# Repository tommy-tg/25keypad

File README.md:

# 25keypad
25 keys Macropad based on RP2040 MCU, programmable, running KMK firmware

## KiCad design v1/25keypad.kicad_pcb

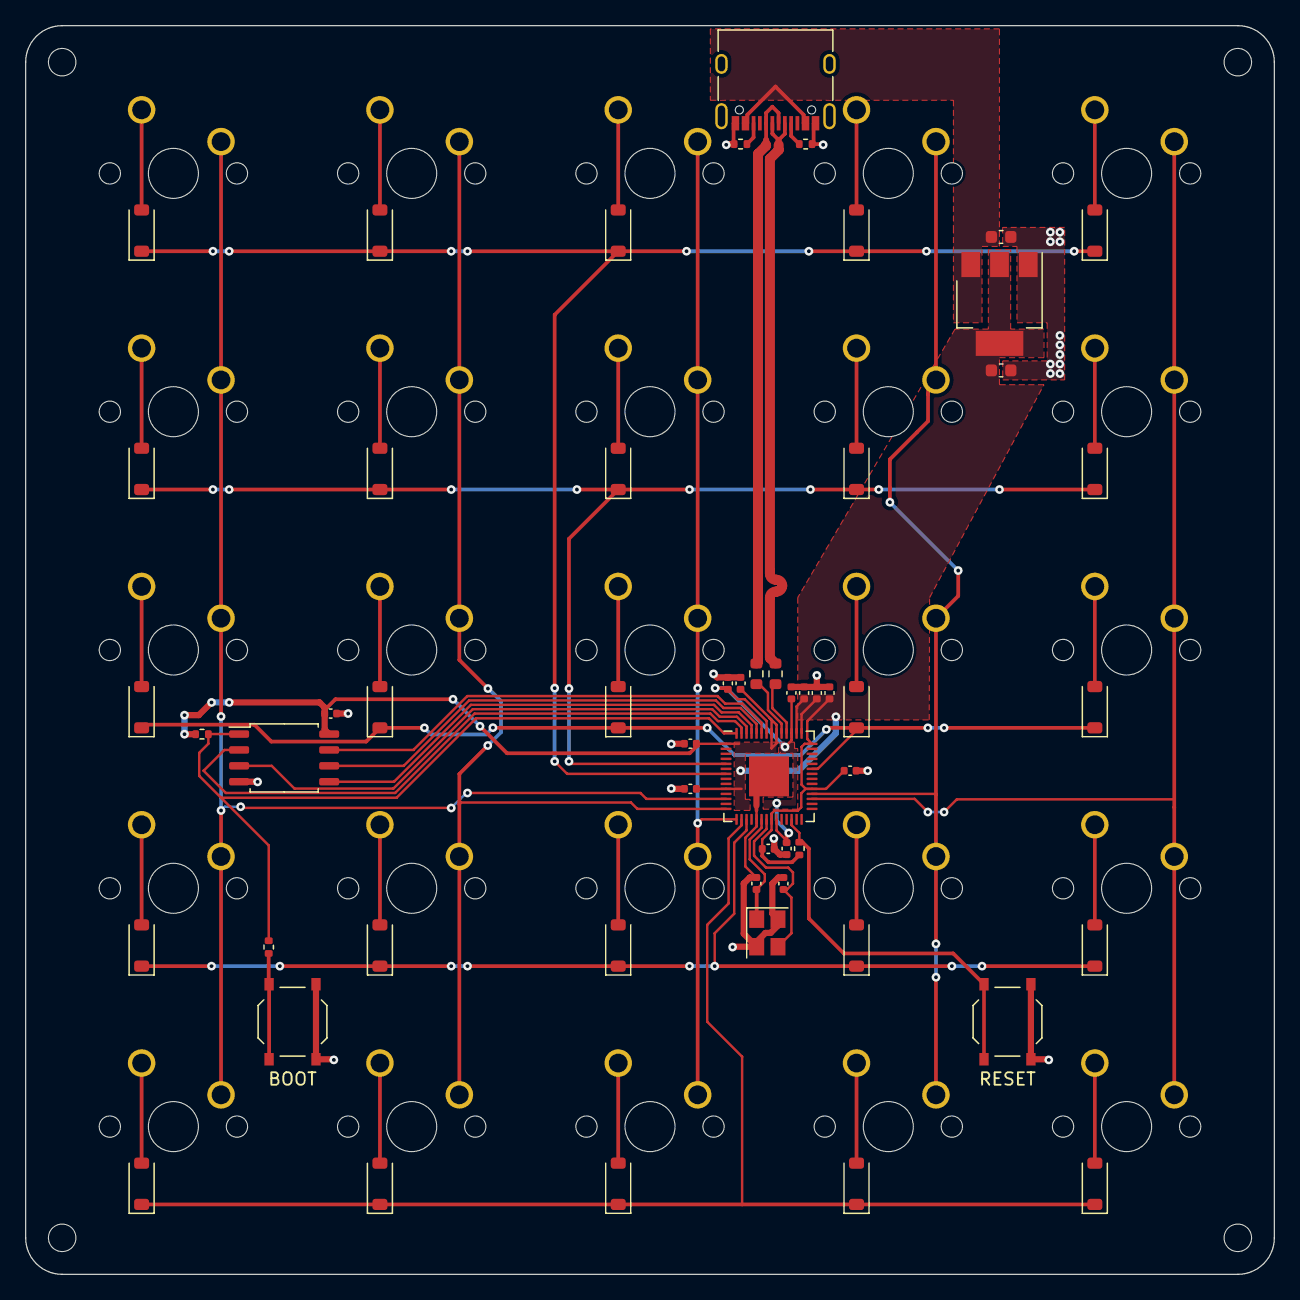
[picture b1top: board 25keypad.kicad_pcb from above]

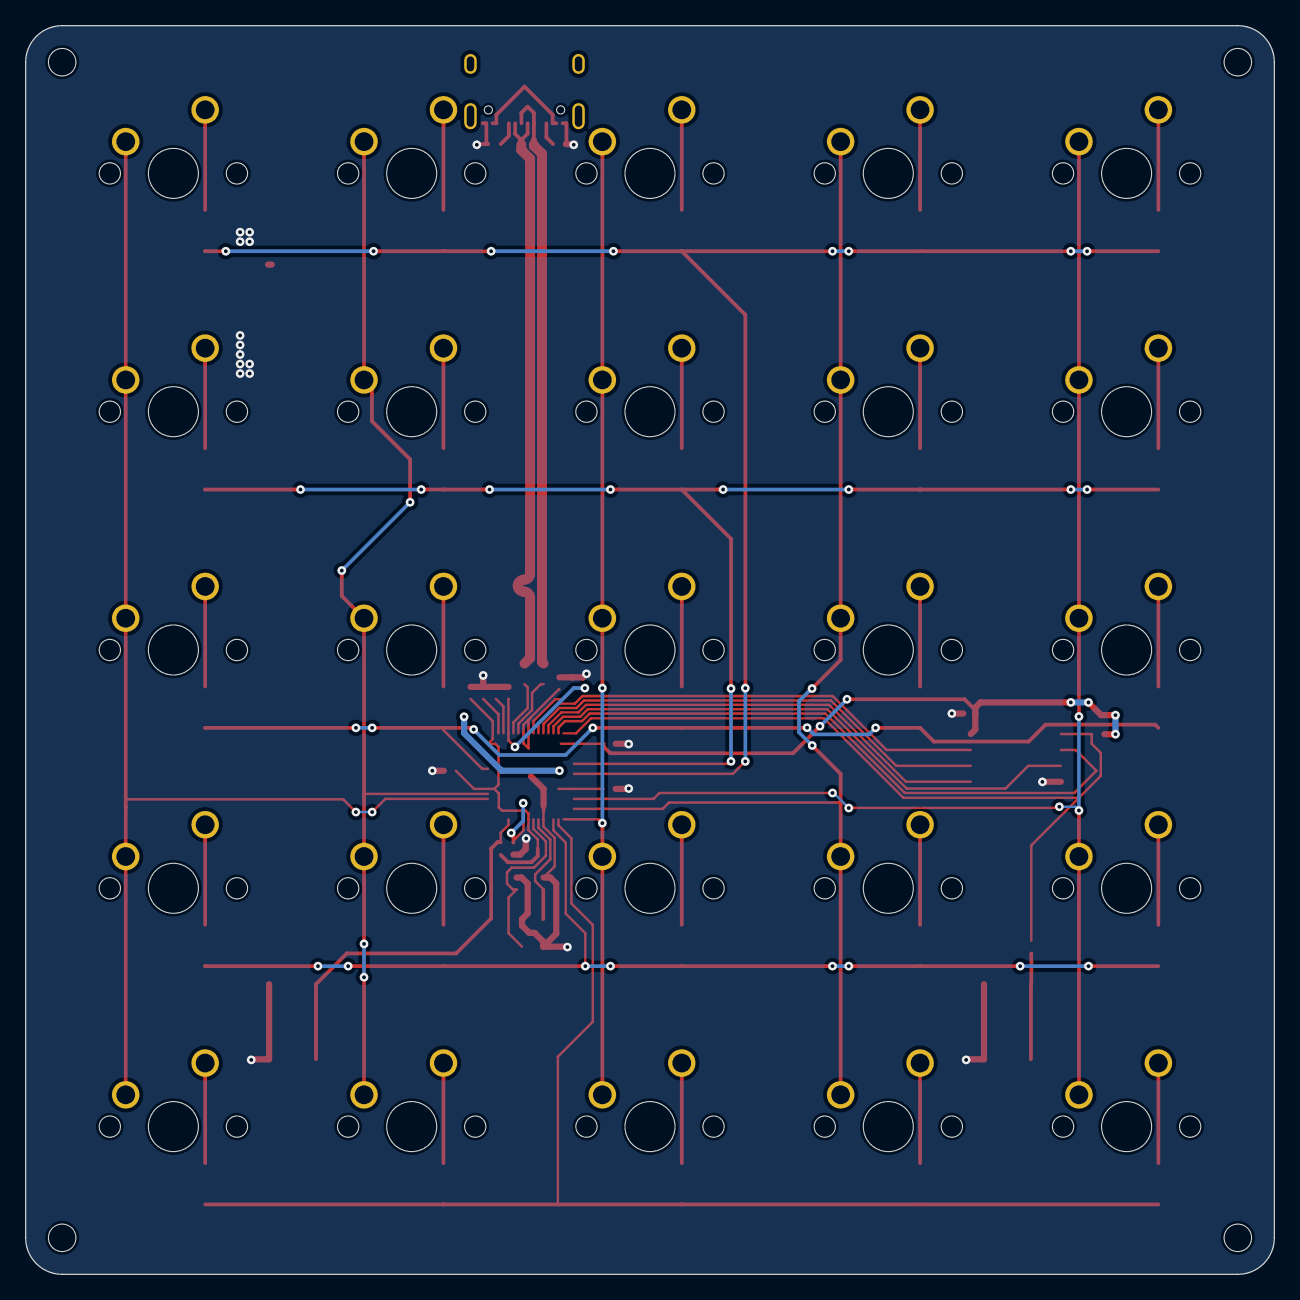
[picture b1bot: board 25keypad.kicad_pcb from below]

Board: 2 copper layers, 99.8 x 99.8 mm, 84 parts (25 on the bottom side), 55 nets.

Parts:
C1, C2, C3, C4, C5, C6, C7, C8, C9, C16: 100n; C_0402_1005Metric
C10, C11: 1u; C_0402_1005Metric
C12, C13: 10u; C_0603_1608Metric
C14, C15: 30p; C_0402_1005Metric
D1, D2, D3, D4, D5, D6, D7, D8, D9, D10, D11, D12, D13, D14, D15, D16, D17, D18, D19, D20, D21, D22, D23, D24, D25: D; D_SOD-123
H1, H2, H3, H4: MountingHole; MountingHole_2.2mm_M2
J1: USB_C_Receptacle_USB2.0; USB_C_Receptacle_XKB_U262-16XN-4BVC11
R1, R2: 27; R_0603_1608Metric
R3: 10k; R_0402_1005Metric
R4, R5: 5k1; R_0402_1005Metric
R6: DNP_10k; R_0402_1005Metric
R7: 1k; R_0402_1005Metric
SW1: KEY_1_00; SW_Cherry_MX_1.00u_PCB_UPDATED_FOOTPRINT_RIGHT_PIN_ASSIGNME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
SW2: KEY_2_01; SW_Cherry_MX_1.00u_PCB_UPDATED_FOOTPRINT_RIGHT_PIN_ASSIGNME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
SW3: KEY_3_02; SW_Cherry_MX_1.00u_PCB_UPDATED_FOOTPRINT_RIGHT_PIN_ASSIGNME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
SW4, SW5, SW10, SW15, SW20, SW25: KEY_4_03; SW_Cherry_MX_1.00u_PCB_UPDATED_FOOTPRINT_RIGHT_PIN_ASSIGNME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
SW6: KEY_5_10; SW_Cherry_MX_1.00u_PCB_UPDATED_FOOTPRINT_RIGHT_PIN_ASSIGNME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
SW7: KEY_6_11; SW_Cherry_MX_1.00u_PCB_UPDATED_FOOTPRINT_RIGHT_PIN_ASSIGNME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
SW8: KEY_7_12; SW_Cherry_MX_1.00u_PCB_UPDATED_FOOTPRINT_RIGHT_PIN_ASSIGNME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
SW9: KEY_8_13; SW_Cherry_MX_1.00u_PCB_UPDATED_FOOTPRINT_RIGHT_PIN_ASSIGNME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
SW11, SW16, SW21: KEY_9_20; SW_Cherry_MX_1.00u_PCB_UPDATED_FOOTPRINT_RIGHT_PIN_ASSIGNME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
SW12, SW17, SW22: KEY_10_21; SW_Cherry_MX_1.00u_PCB_UPDATED_FOOTPRINT_RIGHT_PIN_ASSIGNME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
SW13, SW18, SW23: KEY_11_22; SW_Cherry_MX_1.00u_PCB_UPDATED_FOOTPRINT_RIGHT_PIN_ASSIGNME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
SW14, SW19, SW24: KEY_12_23; SW_Cherry_MX_1.00u_PCB_UPDATED_FOOTPRINT_RIGHT_PIN_ASSIGNME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
SW26, SW27: SW_SPST; SW_Push_1P1T_XKB_TS-1187A
U1: RP2040; QFN-56-1EP_7x7mm_P0.4mm_EP3.2x3.2mm
U2: NCP1117-3.3_SOT223; SOT-223-3_TabPin2
U3: W25Q128JVS; SOIC-8_5.23x5.23mm_P1.27mm
Y1: 12MHz; Crystal_SMD_3225-4Pin_3.2x2.5mm

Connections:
+1V1: C8.2, C9.1, C10.1, U1.23 (DVDD), U1.45 (VREG_VOUT), U1.50 (DVDD)
+3V3: C1.1, C2.1, C3.1, C4.1, C5.1, C6.1, C7.1, C11.1, C13.1, C16.1, R3.2, R6.2, U1.1 (IOVDD), U1.10 (IOVDD), U1.22 (IOVDD), U1.33 (IOVDD), U1.42 (IOVDD), U1.43 (ADC_AVDD), U1.44 (VREG_IN), U1.48 (USB_VDD), U1.49 (IOVDD), U2.2 (VO), U3.8 (VCC)
/COL_0: SW1.1, SW6.1, SW11.1, SW16.1, SW21.1, U1.31 (GPIO20)
/COL_1: SW2.1, SW7.1, SW12.1, SW17.1, SW22.1, U1.32 (GPIO21)
/COL_2: SW3.1, SW8.1, SW13.1, SW18.1, SW23.1, U1.15 (GPIO12)
/COL_3: SW4.1, SW9.1, SW14.1, SW19.1, SW24.1, U1.14 (GPIO11)
/COL_4: SW5.1, SW10.1, SW15.1, SW20.1, SW25.1, U1.12 (GPIO9)
/QSPI_SCLK: U1.52 (QSPI_SCLK), U3.6 (CLK)
/QSPI_SD0: U1.53 (QSPI_SD0), U3.5 (DI(IO0))
/QSPI_SD1: U1.55 (QSPI_SD1), U3.2 (DO(IO1))
/QSPI_SD2: U1.54 (QSPI_SD2), U3.3 (IO2)
/QSPI_SD3: U1.51 (QSPI_SD3), U3.7 (IO3)
/QSPI_SS: R6.1, R7.2, U1.56 (QSPI_SS), U3.1 (~CS)
/ROW_0: D1.1 (K), D2.1 (K), D3.1 (K), D4.1 (K), D5.1 (K), U1.7 (GPIO5)
/ROW_1: D6.1 (K), D7.1 (K), D8.1 (K), D9.1 (K), D10.1 (K), U1.5 (GPIO3)
/ROW_2: D11.1 (K), D12.1 (K), D13.1 (K), D14.1 (K), D15.1 (K), U1.37 (GPIO25)
/ROW_3: D16.1 (K), D17.1 (K), D18.1 (K), D19.1 (K), D20.1 (K), U1.17 (GPIO14)
/ROW_4: D21.1 (K), D22.1 (K), D23.1 (K), D24.1 (K), D25.1 (K), U1.16 (GPIO13)
/USB_D+: J1.A6 (D+), J1.B6 (D+), R1.2
/USB_D-: J1.A7 (D-), J1.B7 (D-), R2.2
/XIN: C14.1, U1.20 (XIN), Y1.1
/XOUT: C15.1, U1.21 (XOUT), Y1.3
/~USB_BOOT: R7.1, SW27.1 (A)
GND: C1.2, C2.2, C3.2, C4.2, C5.2, C6.2, C7.2, C8.1, C9.2, C10.2, C11.2, C12.2, C13.2, C14.2, C15.2, C16.2, J1.A1 (GND), J1.A12 (GND), J1.B1 (GND), J1.B12 (GND), R4.2, R5.2, SW26.1 (A), SW27.2 (B), U1.19 (TESTEN), U1.57 (GND), U2.1 (GND), U3.4 (GND), Y1.2, Y1.4
unnamed: D1.2 (A), SW1.2
unnamed: D2.2 (A), SW2.2
unnamed: D3.2 (A), SW3.2
unnamed: D4.2 (A), SW4.2
unnamed: D5.2 (A), SW5.2
unnamed: D6.2 (A), SW6.2
unnamed: D7.2 (A), SW7.2
unnamed: D8.2 (A), SW8.2
unnamed: D9.2 (A), SW9.2
unnamed: D10.2 (A), SW10.2
unnamed: D11.2 (A), SW11.2
unnamed: D12.2 (A), SW12.2
unnamed: D13.2 (A), SW13.2
unnamed: D14.2 (A), SW14.2
unnamed: D15.2 (A), SW15.2
unnamed: D16.2 (A), SW16.2
unnamed: D17.2 (A), SW17.2
unnamed: D18.2 (A), SW18.2
unnamed: D19.2 (A), SW19.2
unnamed: D20.2 (A), SW20.2
unnamed: D21.2 (A), SW21.2
unnamed: D22.2 (A), SW22.2
unnamed: D23.2 (A), SW23.2
unnamed: D24.2 (A), SW24.2
unnamed: D25.2 (A), SW25.2
unnamed: J1.A5 (CC1), R4.1
unnamed: J1.B5 (CC2), R5.1
unnamed: R3.1, SW26.2 (B), U1.26 (RUN)
unnamed: R2.1, U1.46 (USB_DM)
unnamed: R1.1, U1.47 (USB_DP)
VBUS: C12.1, J1.A4 (VBUS), J1.A9 (VBUS), J1.B4 (VBUS), J1.B9 (VBUS), U2.3 (VI)

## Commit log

2023-10-14 general commit
2023-10-14 add assembled.jpg to README
2023-10-14 add assembled images
2024-04-17 add .gitignore
2024-04-17 add FW folder
2024-04-17 folder refactor and file renaming
2024-04-17 edit README.md
2024-04-17 refactor and file renaming
2024-04-17 remove .gitignore
2024-04-22 add case and plate 3d models
2024-07-12 Create LICENSE
    Add License
2024-09-07 Create LICENSE
